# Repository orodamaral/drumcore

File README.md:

# DRUMCORE — Módulo MIDI-USB/BLE para Bateria Eletrônica (ESP32-S3)

Módulo de disparo MIDI para bateria eletrônica, baseado em ESP32-S3, com suporte a
32 canais analógicos (via 2x multiplexador CD4067, uma "jackboard" de 16 canais
cada — ver [hardware/jackboard/](hardware/jackboard/)), tela TFT ST7735 (SPI) e
1 encoder rotativo com chave para navegação, e um app de configuração em React,
direto pelo navegador via Web Serial — sem instalar nada.

Projeto construído sobre a biblioteca [HelloDrum-arduino-Library](https://github.com/RyoKosaka/HelloDrum-arduino-Library)
de Ryo Kosaka (vendorizada e adaptada em [firmware/lib/HelloDrum-arduino-Library](firmware/lib/HelloDrum-arduino-Library)).

## Estrutura do projeto

```
DrumCore/
├── docs/                 Documentação do projeto (decisões, hardware, progresso)
├── design/               Especificação de UI, identidade visual (logo, paleta)
├── firmware/             Firmware ESP32-S3 (PlatformIO)
│   ├── platformio.ini
│   ├── src/              Código-fonte do módulo
│   ├── include/
│   └── lib/
│       └── HelloDrum-arduino-Library/   Biblioteca base, vendorizada e modificada
├── hardware/             Projetos KiCad (jackboard — placa de conectores TRS + rede de proteção)
├── web-app/              App de configuração do módulo (React/TS), direto no navegador via
│                         Web Serial, sem instalar nada
└── site/                 Site estático de apresentação do projeto (GitHub Pages) — publica
                          o web-app/ em site/app/, ver .github/workflows/pages.yml
```

## Documentação

Todo o histórico de decisões, aprendizados sobre a biblioteca base e notas de
hardware está em [docs/](docs/). Comece por [docs/00-visao-geral.md](docs/00-visao-geral.md).

## Status

Veja [docs/CHANGELOG.md](docs/CHANGELOG.md) para o histórico completo do que já
foi feito.

## Licença

Este projeto é licenciado sob [Creative Commons Atribuição-NãoComercial 4.0
Internacional (CC BY-NC 4.0)](LICENSE) — uso e cópia livres, **sem fins
comerciais**, sempre **citando a fonte** (este repositório e a
HelloDrum-arduino-Library, ver crédito acima). Detalhes completos e a
atribuição de terceiros (a biblioteca base, sob licença MIT própria) estão em
[LICENSE](LICENSE).

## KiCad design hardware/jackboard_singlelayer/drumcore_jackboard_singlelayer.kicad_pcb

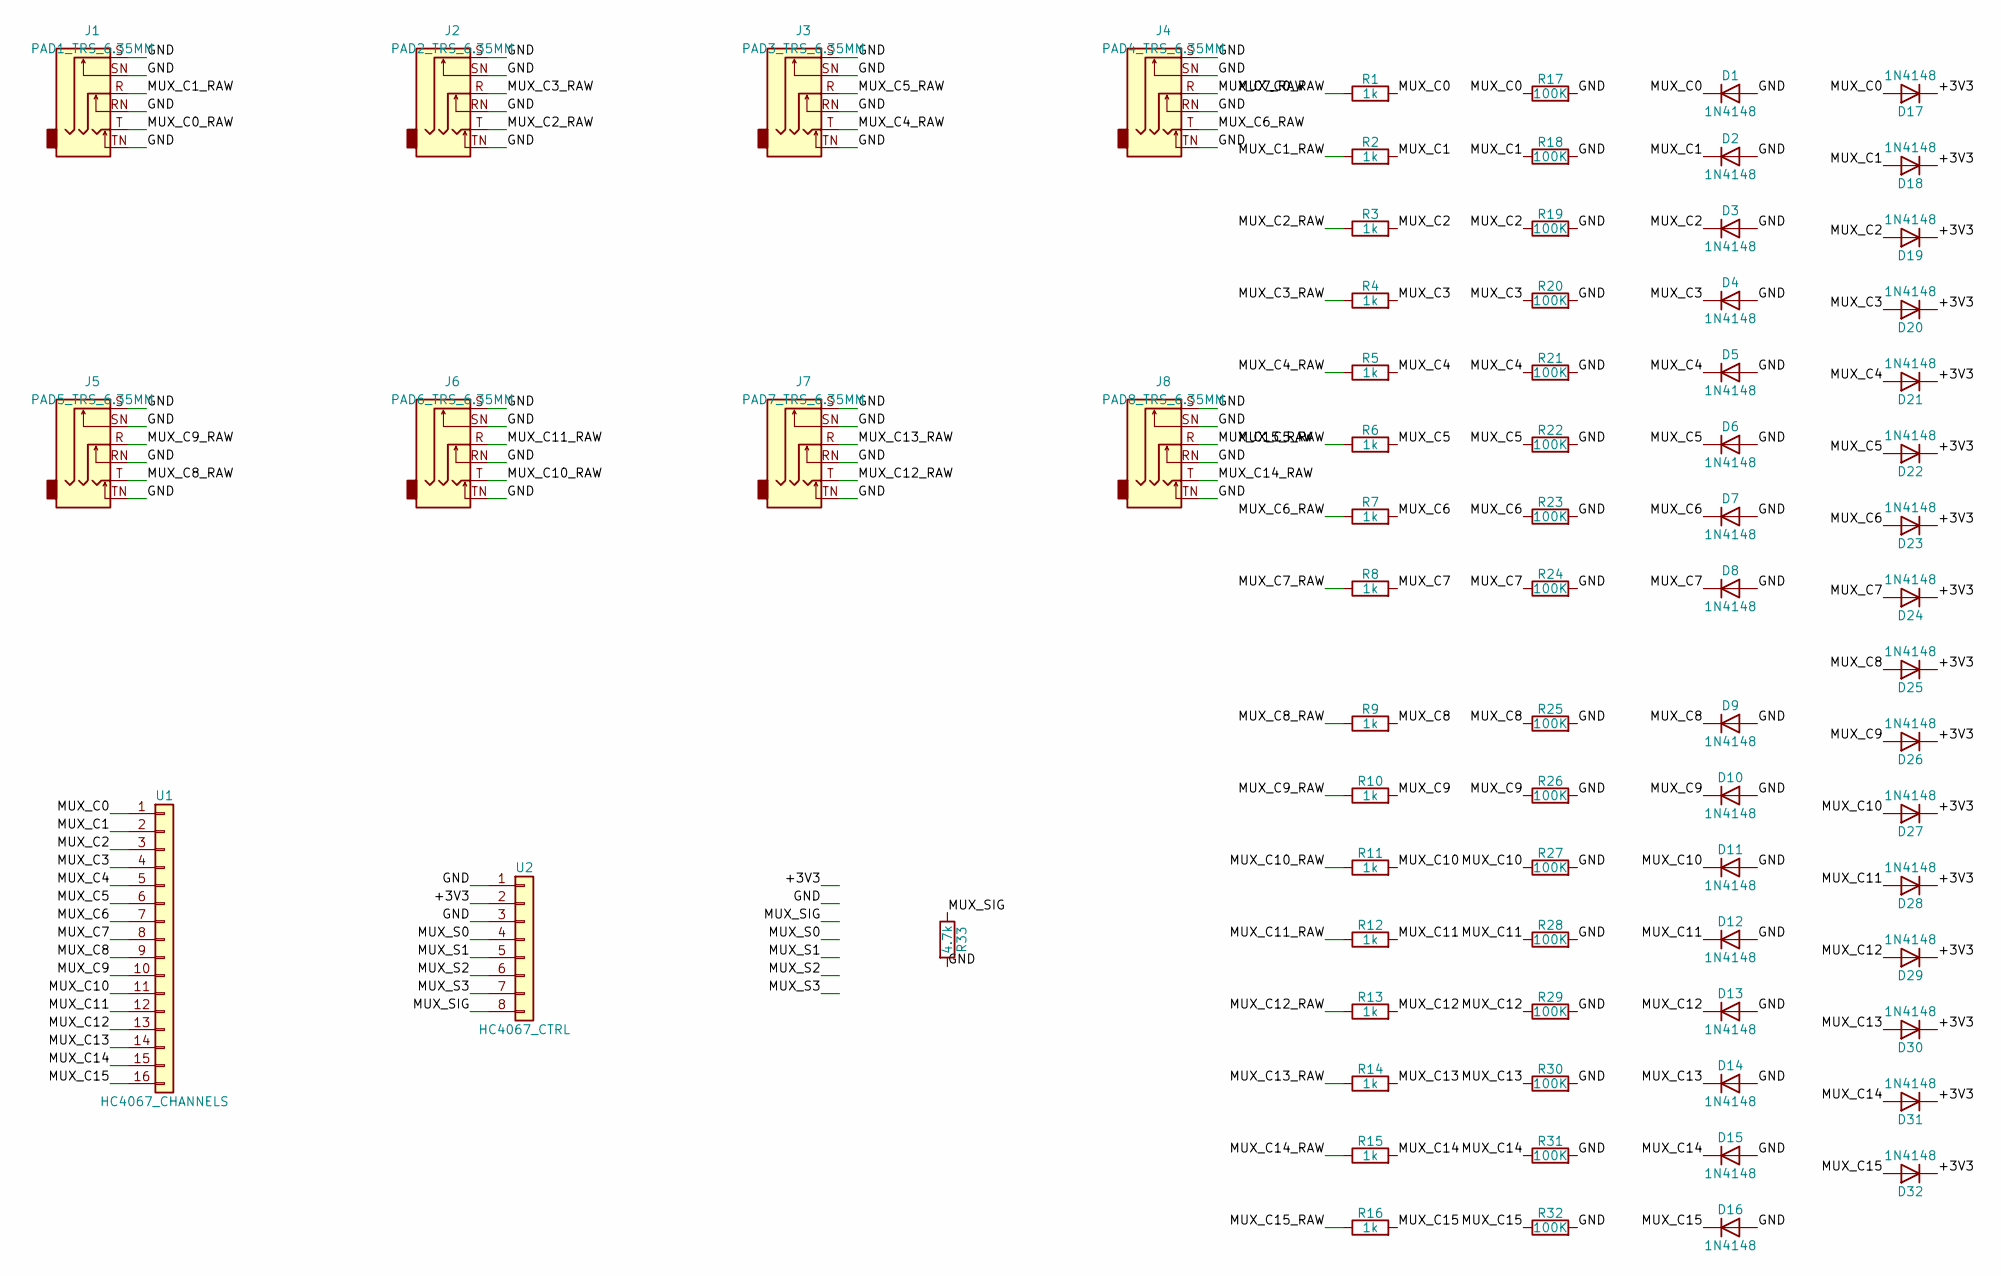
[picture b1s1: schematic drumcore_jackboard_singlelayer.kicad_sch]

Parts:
D1, D2, D3, D4, D5, D6, D7, D8, D9, D10, D11, D12, D13, D14, D15, D16, D17, D18, D19, D20, D21, D22, D23, D24, D25, D26, D27, D28, D29, D30, D31, D32: 1N4148; D_DO-35_SOD27_P7.62mm_Horizontal
J1: PAD1_TRS_6.35MM; Jack_6.35mm_Neutrik_NMJ6HCD2_Horizontal
J2: PAD2_TRS_6.35MM; Jack_6.35mm_Neutrik_NMJ6HCD2_Horizontal
J3: PAD3_TRS_6.35MM; Jack_6.35mm_Neutrik_NMJ6HCD2_Horizontal
J4: PAD4_TRS_6.35MM; Jack_6.35mm_Neutrik_NMJ6HCD2_Horizontal
J5: PAD5_TRS_6.35MM; Jack_6.35mm_Neutrik_NMJ6HCD2_Horizontal
J6: PAD6_TRS_6.35MM; Jack_6.35mm_Neutrik_NMJ6HCD2_Horizontal
J7: PAD7_TRS_6.35MM; Jack_6.35mm_Neutrik_NMJ6HCD2_Horizontal
J8: PAD8_TRS_6.35MM; Jack_6.35mm_Neutrik_NMJ6HCD2_Horizontal
R1, R2, R3, R4, R5, R6, R7, R8, R9, R10, R11, R12, R13, R14, R15, R16: 1k; R_Axial_DIN0207_L6.3mm_D2.5mm_P7.62mm_Horizontal
R17, R18, R19, R20, R21, R22, R23, R24, R25, R26, R27, R28, R29, R30, R31, R32: 100K; R_Axial_DIN0207_L6.3mm_D2.5mm_P7.62mm_Horizontal
R33: 4.7k; R_Axial_DIN0207_L6.3mm_D2.5mm_P7.62mm_Horizontal
U1: HC4067_CHANNELS; PinSocket_1x16_P2.54mm_Vertical
U2: HC4067_CTRL; PinSocket_1x08_P2.54mm_Vertical

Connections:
/+3V3: D17.1 (K), D18.1 (K), D19.1 (K), D20.1 (K), D21.1 (K), D22.1 (K), D23.1 (K), D24.1 (K), D25.1 (K), D26.1 (K), D27.1 (K), D28.1 (K), D29.1 (K), D30.1 (K), D31.1 (K), D32.1 (K), U2.2
/GND: D1.2 (A), D2.2 (A), D3.2 (A), D4.2 (A), D5.2 (A), D6.2 (A), D7.2 (A), D8.2 (A), D9.2 (A), D10.2 (A), D11.2 (A), D12.2 (A), D13.2 (A), D14.2 (A), D15.2 (A), D16.2 (A), J1.RN, J1.S, J1.SN, J1.TN, J2.RN, J2.S, J2.SN, J2.TN, J3.RN, J3.S, J3.SN, J3.TN, J4.RN, J4.S, J4.SN, J4.TN, J5.RN, J5.S, J5.SN, J5.TN, J6.RN, J6.S, J6.SN, J6.TN, J7.RN, J7.S, J7.SN, J7.TN, J8.RN, J8.S, J8.SN, J8.TN, R17.2, R18.2, R19.2, R20.2, R21.2, R22.2, R23.2, R24.2, R25.2, R26.2, R27.2, R28.2, R29.2, R30.2, R31.2, R32.2, R33.2, U2.1, U2.3
/MUX_C0: D1.1 (K), D17.2 (A), R1.2, R17.1, U1.1
/MUX_C0_RAW: J1.T, R1.1
/MUX_C1: D2.1 (K), D18.2 (A), R2.2, R18.1, U1.2
/MUX_C1_RAW: J1.R, R2.1
/MUX_C2: D3.1 (K), D19.2 (A), R3.2, R19.1, U1.3
/MUX_C2_RAW: J2.T, R3.1
/MUX_C3: D4.1 (K), D20.2 (A), R4.2, R20.1, U1.4
/MUX_C3_RAW: J2.R, R4.1
/MUX_C4: D5.1 (K), D21.2 (A), R5.2, R21.1, U1.5
/MUX_C4_RAW: J3.T, R5.1
/MUX_C5: D6.1 (K), D22.2 (A), R6.2, R22.1, U1.6
/MUX_C5_RAW: J3.R, R6.1
/MUX_C6: D7.1 (K), D23.2 (A), R7.2, R23.1, U1.7
/MUX_C6_RAW: J4.T, R7.1
/MUX_C7: D8.1 (K), D24.2 (A), R8.2, R24.1, U1.8
/MUX_C7_RAW: J4.R, R8.1
/MUX_C8: D9.1 (K), D25.2 (A), R9.2, R25.1, U1.9
/MUX_C8_RAW: J5.T, R9.1
/MUX_C9: D10.1 (K), D26.2 (A), R10.2, R26.1, U1.10
/MUX_C9_RAW: J5.R, R10.1
/MUX_C10: D11.1 (K), D27.2 (A), R11.2, R27.1, U1.11
/MUX_C10_RAW: J6.T, R11.1
/MUX_C11: D12.1 (K), D28.2 (A), R12.2, R28.1, U1.12
/MUX_C11_RAW: J6.R, R12.1
/MUX_C12: D13.1 (K), D29.2 (A), R13.2, R29.1, U1.13
/MUX_C12_RAW: J7.T, R13.1
/MUX_C13: D14.1 (K), D30.2 (A), R14.2, R30.1, U1.14
/MUX_C13_RAW: J7.R, R14.1
/MUX_C14: D15.1 (K), D31.2 (A), R15.2, R31.1, U1.15
/MUX_C14_RAW: J8.T, R15.1
/MUX_C15: D16.1 (K), D32.2 (A), R16.2, R32.1, U1.16
/MUX_C15_RAW: J8.R, R16.1
/MUX_S0: U2.4
/MUX_S1: U2.5
/MUX_S2: U2.6
/MUX_S3: U2.7
/MUX_SIG: R33.1, U2.8

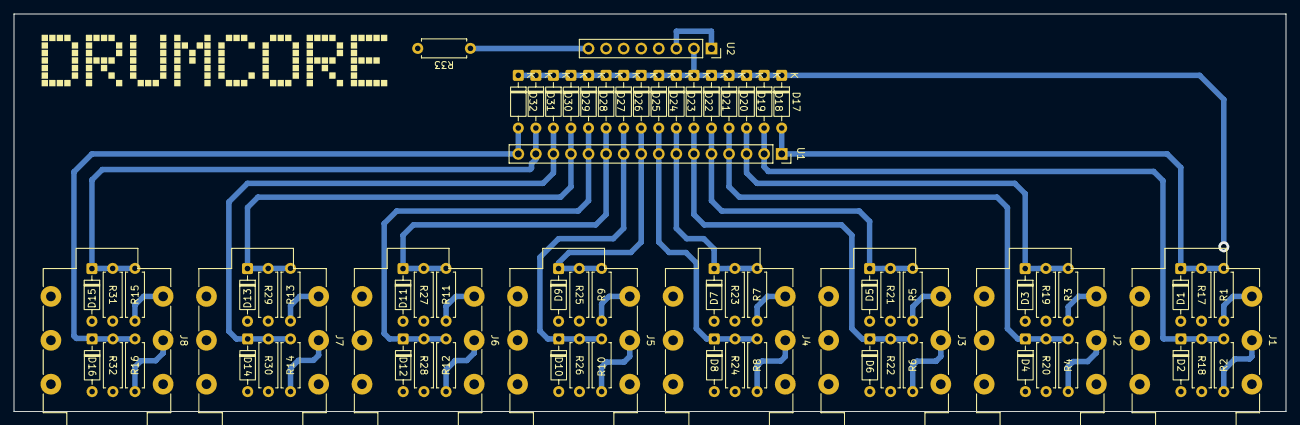
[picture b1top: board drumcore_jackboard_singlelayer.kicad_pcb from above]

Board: 2 copper layers, 184.0 x 57.5 mm, 75 parts (0 on the bottom side), 35 nets.

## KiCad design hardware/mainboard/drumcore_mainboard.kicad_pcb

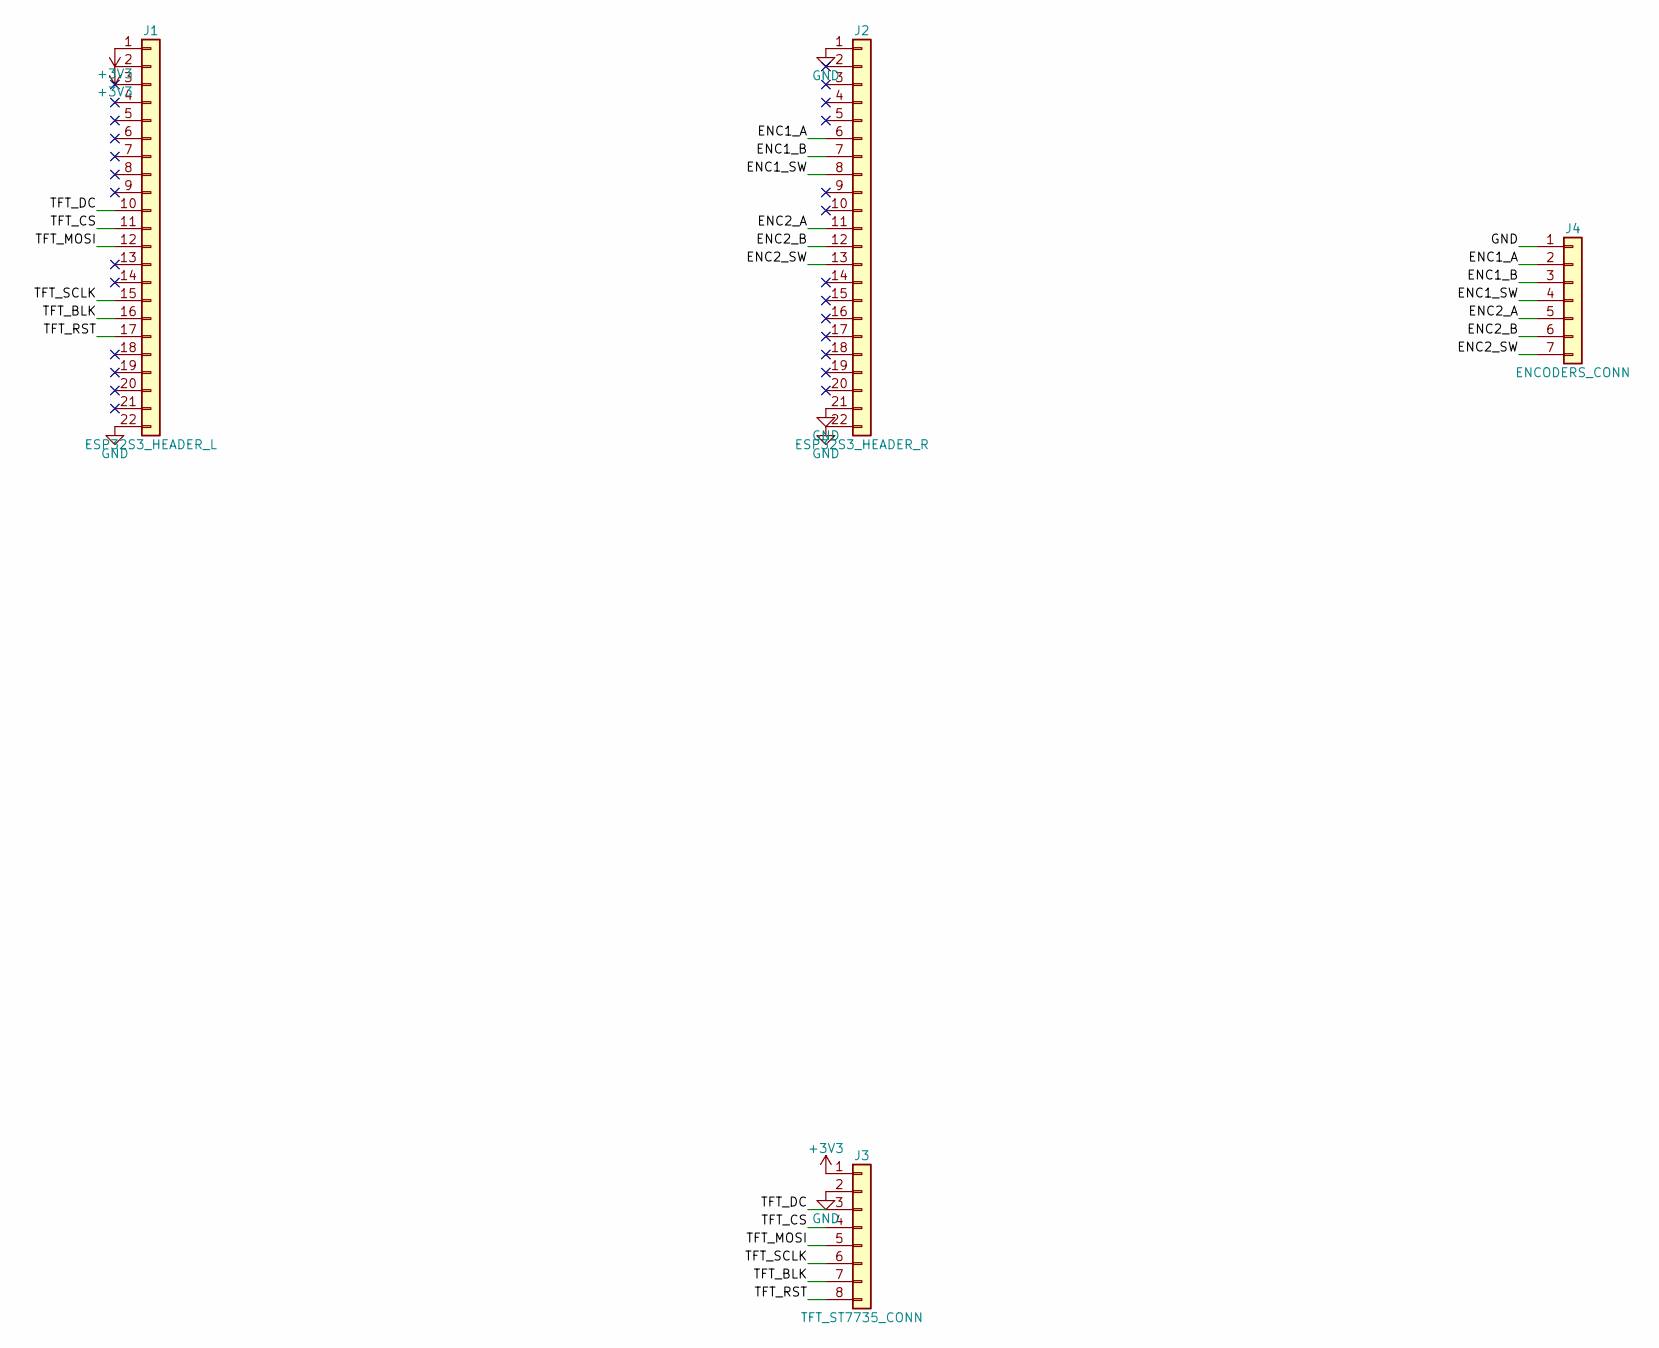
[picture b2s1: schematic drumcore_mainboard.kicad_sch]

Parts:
J1: ESP32S3_HEADER_L; PinSocket_1x22_P2.54mm_Vertical
J2: ESP32S3_HEADER_R; PinSocket_1x22_P2.54mm_Vertical
J3: TFT_ST7735_CONN; PinHeader_1x08_P2.54mm_Vertical
J4: ENCODERS_CONN; PinHeader_1x07_P2.54mm_Vertical

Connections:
+3V3: J1.1, J1.2, J3.1
/ENC1_A: J2.6, J4.2
/ENC1_B: J2.7, J4.3
/ENC1_SW: J2.8, J4.4
/ENC2_A: J2.11, J4.5
/ENC2_B: J2.12, J4.6
/ENC2_SW: J2.13, J4.7
/TFT_BLK: J1.16, J3.7
/TFT_CS: J1.11, J3.4
/TFT_DC: J1.10, J3.3
/TFT_MOSI: J1.12, J3.5
/TFT_RST: J1.17, J3.8
/TFT_SCLK: J1.15, J3.6
GND: J1.22, J2.1, J2.21, J2.22, J3.2, J4.1

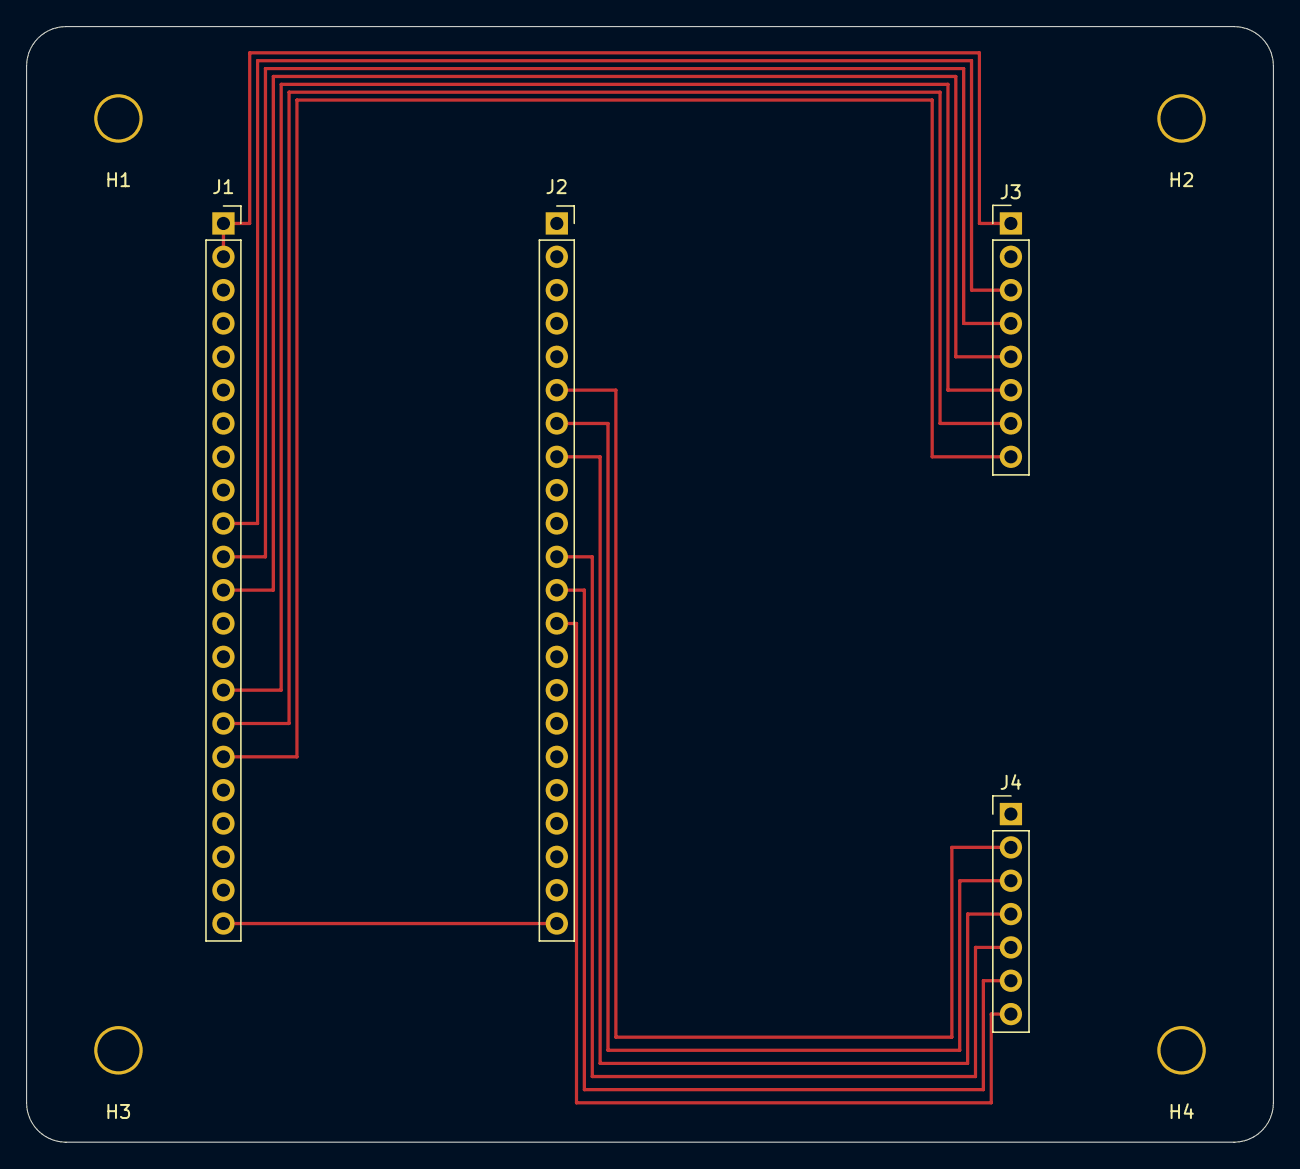
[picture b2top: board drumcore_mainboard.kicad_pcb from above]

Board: 2 copper layers, 95.0 x 85.0 mm, 8 parts (0 on the bottom side), 14 nets.

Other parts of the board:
H1, H2, H3, H4: MountingHole; MountingHole_3.2mm

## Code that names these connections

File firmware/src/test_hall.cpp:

/*
  Teste isolado do sensor hall (SS49E) no RING do jack 1 (canal 1 do MUX da
  jackboard A, 2026-10-01 - antes era o GPIO9 direto) - mostra a leitura bruta do
  ADC (0-4095) na tela TFT e no Serial, ao vivo. Sem MUX/encoders/USB-MIDI/
  BLE/EEPROM do firmware principal - so' pra confirmar que o sensor esta'
  ligado certo e respondendo (valor sobe/desce ao aproximar um ima).

  Uso: `pio run -e test_hall -t upload --upload-port COM5`
  (ver [env:test_hall] em platformio.ini - so compila este arquivo, main.cpp
  fica de fora dessa build).

  Mesmos pinos de tela do main.cpp (Fase Z + ajuste 2026-09-06, ver
  docs/02-hardware.md): SCL=7, SDA=15, RES=16, DC=17, CS=18, BLK=8.
  Sensor hall no jack 1: tip = VCC (3V3 via 47R na jackboard), ring = OUT
  (canal 1 do MUX), sleeve = GND. MUX: S0=39 S1=40 S2=41 S3=42, SIG=GPIO2.
*/

#include <Arduino.h>
#include <SPI.h>
#include <Adafruit_GFX.h>
#include <Adafruit_ST7735.h>

#define TFT_SCLK 7
#define TFT_MOSI 15
#define TFT_RST 16
#define TFT_DC 17
#define TFT_CS 18
#define TFT_BLK 8

#define MUX_S0 39
#define MUX_S1 40
#define MUX_S2 41
#define MUX_S3 42
#define MUX_SIG 2
#define HALL_MUX_CH 1 // ring do jack 1

// Mesma paleta do main.cpp (design/SPEC.md) - RGB565.
#define COL_BG 0x10A3
#define COL_TXT 0xE77E
#define COL_TXT_DIM 0x7C52
#define COL_ACCENT 0x069F

Adafruit_ST7735 tft(TFT_CS, TFT_DC, TFT_RST);

void setup()
{
    Serial.begin(115200);

    // Endereco fixo no canal do sensor - nao precisa trocar durante o teste.
    pinMode(MUX_S0, OUTPUT);
    pinMode(MUX_S1, OUTPUT);
    pinMode(MUX_S2, OUTPUT);
    pinMode(MUX_S3, OUTPUT);
    digitalWrite(MUX_S0, HALL_MUX_CH & 1);
    digitalWrite(MUX_S1, (HALL_MUX_CH >> 1) & 1);
    digitalWrite(MUX_S2, (HALL_MUX_CH >> 2) & 1);
    digitalWrite(MUX_S3, (HALL_MUX_CH >> 3) & 1);

    pinMode(TFT_BLK, OUTPUT);
    digitalWrite(TFT_BLK, HIGH); // backlight sempre ligado, sem PWM

    SPI.begin(TFT_SCLK, -1 /* MISO nao usado */, TFT_MOSI, TFT_CS);
    tft.initR(INITR_BLACKTAB); // confirmado em hardware real
    tft.setRotation(0);

    tft.fillScreen(COL_BG);
    tft.setTextColor(COL_ACCENT);
    tft.setTextSize(1);
    tft.setCursor(14, 20);
    tft.print("TESTE SENSOR HALL");
    tft.setCursor(30, 34);
    tft.print("J1 ring - raw ADC");
}

void loop()
{
    int raw = analogRead(MUX_SIG); // 0-4095 (ADC de 12 bits)

    // Redesenha so' a area do numero, pra nao piscar a tela toda.
    tft.fillRect(0, 55, 160, 40, COL_BG);
    tft.setTextColor(COL_TXT);
    tft.setTextSize(4);
    tft.setCursor(raw < 1000 ? (raw < 100 ? (raw < 10 ? 60 : 40) : 20) : 0, 60);
    tft.print(raw);

    tft.setTextSize(1);
    tft.setTextColor(COL_TXT_DIM);
    tft.setCursor(14, 105);
    tft.print("faixa: 0 (min) - 4095 (max)");

    Serial.println(raw);

    delay(100);
}
